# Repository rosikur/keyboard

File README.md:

# keyboard

I dont know what to call it so lets call it "keeb" because thats the name  of  the guide

This was my first keyboard , apart from my macropad ,the keyboard took 3 times , more on that on my Journal

## Features
- Us keyboard
- Del key with fn + Backspace
- 75 %
- Made with lots of hate and Caffeine
- Rotary Encoder
## How to assemble
First you go to jlcpcb and uplood the gerber files, i recommend black pcb colors
Then you go to Aliexpress and order all the parts from the BOM

In the meantime while it ships you start printing the Case,if your Printer is too small , half it or you can order it off print legion

Once everything is ready , you grab some solder and an iron , i recommend leaded solder makes it easier,firstly take your pi pico and add the  male pins,then put it trough and solder everything and snap off its legs outside

Then take your diodes,and turn the board around ,make sure the diodes are pointing  down in orientation and solder them,snap off its legs 

Then take your switchs,turn the board around and pit them all in and solder them one by one 

Last but not least ,add the rotary encoder and solder it

Also add the Stabalizers , watch a tiktok to put them togehter

put the ready board in the case add heated inserts and screw it together

add the key caps and youre done with assembly:D

## How to Software 
Set the Pi Pico to its Bootloader and connect it to your pc  take the uf2 zip and unzip , 

move the file to the pi labelled usb driver

thats it have fun! 

## Picture Gallary

## Bill of Materials

| Item | QNT | Price | Link | Details |
| --- | --- | --- | --- | --- |
| Switches | 162 | 13.39/45 * 4 = 53.56 EUR = 62.48 USD | [AliExpress](https://a.aliexpress.com/_EJTCEpM) | AKKO v3 pro cream blue |
| Keycaps | 2 sets | 16.99 EUR * 2 = 33.98 EUR = 39.64 USD | [AliExpress](https://a.aliexpress.com/_Eyr32DU) | Cuul MC keycaps |
| Diodes | 160 | 1.39 * 2 + duties = 5.78 | [AliExpress](https://a.aliexpress.com/_EGyImLY) | |
| Rotary Encoder | 2 | 6.49 + duties 3 EUR = 9.49 EUR | [AliExpress](https://a.aliexpress.com/_EjwhFqK) | |
| Orpheus Pico | 2 | 3.05 * 2 + duties = 9.10 | [AliExpress](https://a.aliexpress.com/_ExrMmQe) | In reality, it is a knockoff Pi Pico |
| PCB | | 37.39 | | |
| Cable | | 6.49 + duties = 9.49 | [AliExpress](https://a.aliexpress.com/_EwkdJdC) | |
| MX Stab | | 6.19 + duties = 9.19 | [AliExpress](https://a.aliexpress.com/_EHf4OAA) | |
| **Total** | | **167.98 EUR = 196.01 USD** | | |

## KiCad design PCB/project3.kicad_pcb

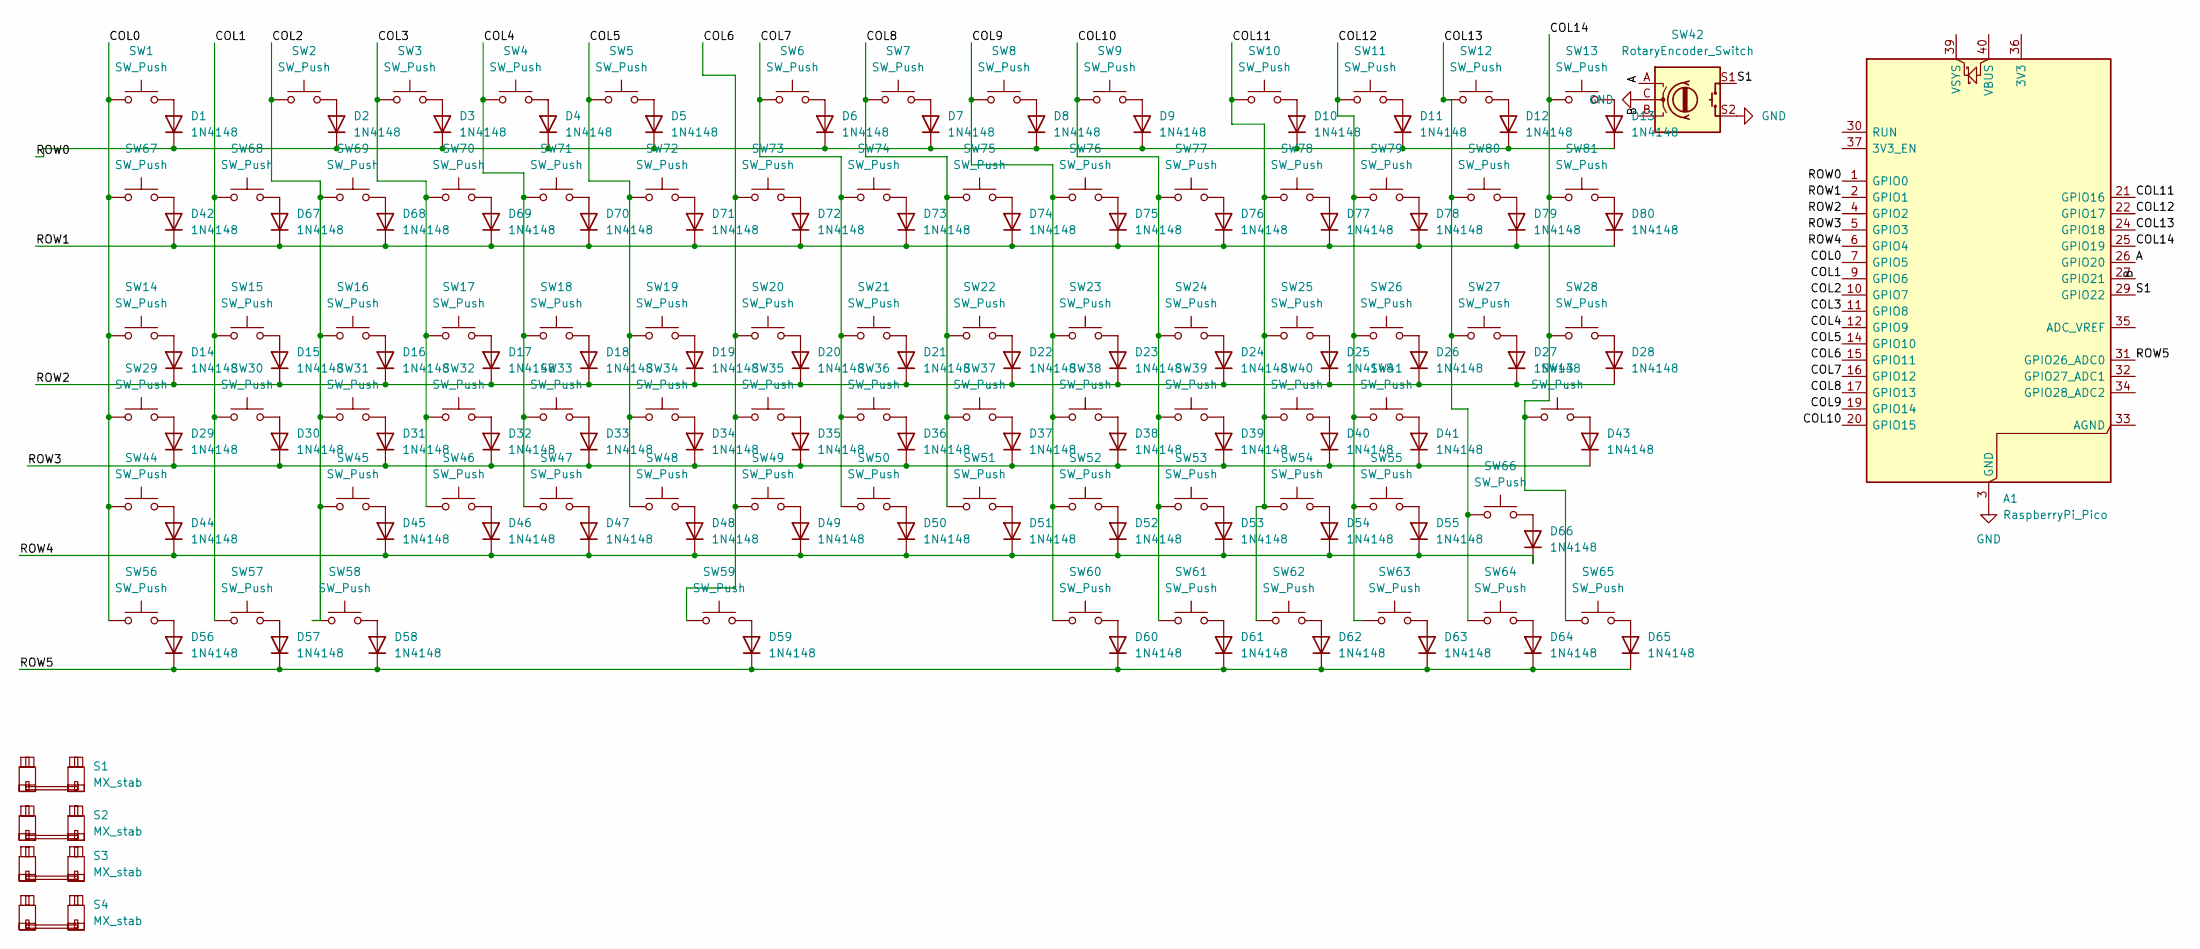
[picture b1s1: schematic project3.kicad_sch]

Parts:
A1: RaspberryPi_Pico; RaspberryPi_Pico_Common_Unspecified
D1, D2, D3, D4, D5, D6, D7, D8, D9, D10, D11, D12, D13, D14, D15, D16, D17, D18, D19, D20, D21, D22, D23, D24, D25, D26, D27, D28, D29, D30, D31, D32, D33, D34, D35, D36, D37, D38, D39, D40, D41, D42, D43, D44, D45, D46, D47, D48, D49, D50, D51, D52, D53, D54, D55, D56, D57, D58, D59, D60, D61, D62, D63, D64, D65, D66, D67, D68, D69, D70, D71, D72, D73, D74, D75, D76, D77, D78, D79, D80: 1N4148; D_DO-35_SOD27_P7.62mm_Horizontal
S1: MX_stab; STAB_MX_P_6.25u
S2, S3, S4: MX_stab; STAB_MX_2.25u
SW1, SW2, SW3, SW4, SW5, SW6, SW7, SW8, SW9, SW10, SW11, SW12, SW13, SW14, SW15, SW16, SW17, SW18, SW19, SW20, SW21, SW22, SW23, SW24, SW25, SW26, SW27, SW28, SW29, SW30, SW31, SW32, SW33, SW34, SW35, SW36, SW37, SW38, SW39, SW40, SW41, SW43, SW44, SW45, SW46, SW47, SW48, SW49, SW50, SW51, SW52, SW53, SW54, SW55, SW56, SW57, SW58, SW59, SW60, SW61, SW62, SW63, SW64, SW65, SW66, SW67, SW68, SW69, SW70, SW71, SW72, SW73, SW74, SW75, SW76, SW77, SW78, SW79, SW80, SW81: SW_Push; SW_MX_1u
SW42: RotaryEncoder_Switch; RotaryEncoder_Alps_EC11E-Switch_Vertical_H20mm

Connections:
/A: A1.26 (GPIO20), SW42.A
/B: A1.27 (GPIO21), SW42.B
/COL0: A1.7 (GPIO5), SW1.1, SW14.1, SW29.1, SW44.1, SW56.1, SW67.1
/COL1: A1.9 (GPIO6), SW15.1, SW30.1, SW57.1, SW68.1
/COL2: A1.10 (GPIO7), SW2.1, SW16.1, SW31.1, SW45.1, SW58.1, SW69.1
/COL4: A1.12 (GPIO9), SW4.1, SW18.1, SW33.1, SW47.1, SW71.1
/COL5: A1.14 (GPIO10), SW5.1, SW19.1, SW34.1, SW48.1, SW72.1
/COL6: A1.15 (GPIO11), SW20.1, SW35.1, SW49.1, SW59.1, SW73.1
/COL7: A1.16 (GPIO12), SW6.1, SW21.1, SW36.1, SW50.1, SW74.1
/COL8: A1.17 (GPIO13), SW7.1, SW22.1, SW37.1, SW51.1, SW75.1
/COL9: A1.19 (GPIO14), SW8.1, SW23.1, SW38.1, SW52.1, SW60.1, SW76.1
/COL10: A1.20 (GPIO15), SW9.1, SW24.1, SW39.1, SW53.1, SW61.1, SW77.1
/COL11: A1.21 (GPIO16), SW10.1, SW25.1, SW40.1, SW54.1, SW62.1, SW78.1
/COL12: A1.22 (GPIO17), SW11.1, SW26.1, SW41.1, SW55.1, SW63.1, SW79.1
/COL13: A1.24 (GPIO18), SW12.1, SW27.1, SW64.1, SW66.1, SW80.1
/COL14: A1.25 (GPIO19), SW13.1, SW28.1, SW43.1, SW65.1, SW81.1
/ROW0: A1.1 (GPIO0), D1.1 (K), D2.1 (K), D3.1 (K), D4.1 (K), D5.1 (K), D6.1 (K), D7.1 (K), D8.1 (K), D9.1 (K), D10.1 (K), D11.1 (K), D12.1 (K), D13.1 (K)
/ROW1: A1.2 (GPIO1), D42.1 (K), D67.1 (K), D68.1 (K), D69.1 (K), D70.1 (K), D71.1 (K), D72.1 (K), D73.1 (K), D74.1 (K), D75.1 (K), D76.1 (K), D77.1 (K), D78.1 (K), D79.1 (K), D80.1 (K)
/ROW2: A1.4 (GPIO2), D14.1 (K), D15.1 (K), D16.1 (K), D17.1 (K), D18.1 (K), D19.1 (K), D20.1 (K), D21.1 (K), D22.1 (K), D23.1 (K), D24.1 (K), D25.1 (K), D26.1 (K), D27.1 (K), D28.1 (K)
/ROW3: A1.5 (GPIO3), D29.1 (K), D30.1 (K), D31.1 (K), D32.1 (K), D33.1 (K), D34.1 (K), D35.1 (K), D36.1 (K), D37.1 (K), D38.1 (K), D39.1 (K), D40.1 (K), D41.1 (K), D43.1 (K)
/ROW4: A1.6 (GPIO4), D44.1 (K), D45.1 (K), D46.1 (K), D47.1 (K), D48.1 (K), D49.1 (K), D50.1 (K), D51.1 (K), D52.1 (K), D53.1 (K), D54.1 (K), D55.1 (K), D66.1 (K)
/ROW5: A1.31 (GPIO26_ADC0), D56.1 (K), D57.1 (K), D58.1 (K), D59.1 (K), D60.1 (K), D61.1 (K), D62.1 (K), D63.1 (K), D64.1 (K), D65.1 (K)
/S1: A1.29 (GPIO22), SW42.S1
GND: A1.3 (GND), A1.8 (GND), A1.13 (GND), A1.18 (GND), A1.23 (GND), A1.28 (GND), A1.38 (GND), SW42.C, SW42.S2
unnamed: D1.2 (A), SW1.2
unnamed: D2.2 (A), SW2.2
unnamed: D3.2 (A), SW3.2
unnamed: D4.2 (A), SW4.2
unnamed: D5.2 (A), SW5.2
unnamed: D6.2 (A), SW6.2
unnamed: D7.2 (A), SW7.2
unnamed: D8.2 (A), SW8.2
unnamed: D9.2 (A), SW9.2
unnamed: D10.2 (A), SW10.2
unnamed: D11.2 (A), SW11.2
unnamed: D12.2 (A), SW12.2
unnamed: D13.2 (A), SW13.2
unnamed: D14.2 (A), SW14.2
unnamed: D15.2 (A), SW15.2
unnamed: D16.2 (A), SW16.2
unnamed: D17.2 (A), SW17.2
unnamed: D18.2 (A), SW18.2
unnamed: D19.2 (A), SW19.2
unnamed: D20.2 (A), SW20.2
unnamed: D21.2 (A), SW21.2
unnamed: D22.2 (A), SW22.2
unnamed: D23.2 (A), SW23.2
unnamed: D24.2 (A), SW24.2
unnamed: D25.2 (A), SW25.2
unnamed: D26.2 (A), SW26.2
unnamed: D27.2 (A), SW27.2
unnamed: D28.2 (A), SW28.2
unnamed: D29.2 (A), SW29.2
unnamed: D30.2 (A), SW30.2
unnamed: D31.2 (A), SW31.2
unnamed: D32.2 (A), SW32.2
unnamed: D33.2 (A), SW33.2
unnamed: D34.2 (A), SW34.2
unnamed: D35.2 (A), SW35.2
unnamed: D36.2 (A), SW36.2
unnamed: D37.2 (A), SW37.2
unnamed: D38.2 (A), SW38.2
unnamed: D39.2 (A), SW39.2
unnamed: D40.2 (A), SW40.2
unnamed: D41.2 (A), SW41.2
unnamed: D42.2 (A), SW67.2
unnamed: D43.2 (A), SW43.2
unnamed: D44.2 (A), SW44.2
unnamed: D45.2 (A), SW45.2
unnamed: D46.2 (A), SW46.2
unnamed: D47.2 (A), SW47.2
unnamed: D48.2 (A), SW48.2
unnamed: D49.2 (A), SW49.2
unnamed: D50.2 (A), SW50.2
unnamed: D51.2 (A), SW51.2
unnamed: D52.2 (A), SW52.2
unnamed: D53.2 (A), SW53.2
unnamed: D54.2 (A), SW54.2
unnamed: D55.2 (A), SW55.2
unnamed: D56.2 (A), SW56.2
unnamed: D57.2 (A), SW57.2
unnamed: D58.2 (A), SW58.2
unnamed: D59.2 (A), SW59.2
unnamed: D60.2 (A), SW60.2
unnamed: D61.2 (A), SW61.2
unnamed: D62.2 (A), SW62.2
unnamed: D63.2 (A), SW63.2
unnamed: D64.2 (A), SW64.2
unnamed: D65.2 (A), SW65.2
unnamed: D66.2 (A), SW66.2
unnamed: D67.2 (A), SW68.2
unnamed: D68.2 (A), SW69.2
unnamed: D70.2 (A), SW71.2
unnamed: D71.2 (A), SW72.2
unnamed: D72.2 (A), SW73.2
unnamed: D73.2 (A), SW74.2
unnamed: D74.2 (A), SW75.2
unnamed: D75.2 (A), SW76.2
unnamed: D76.2 (A), SW77.2
unnamed: D77.2 (A), SW78.2
unnamed: D78.2 (A), SW79.2
unnamed: D79.2 (A), SW80.2
unnamed: D80.2 (A), SW81.2

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
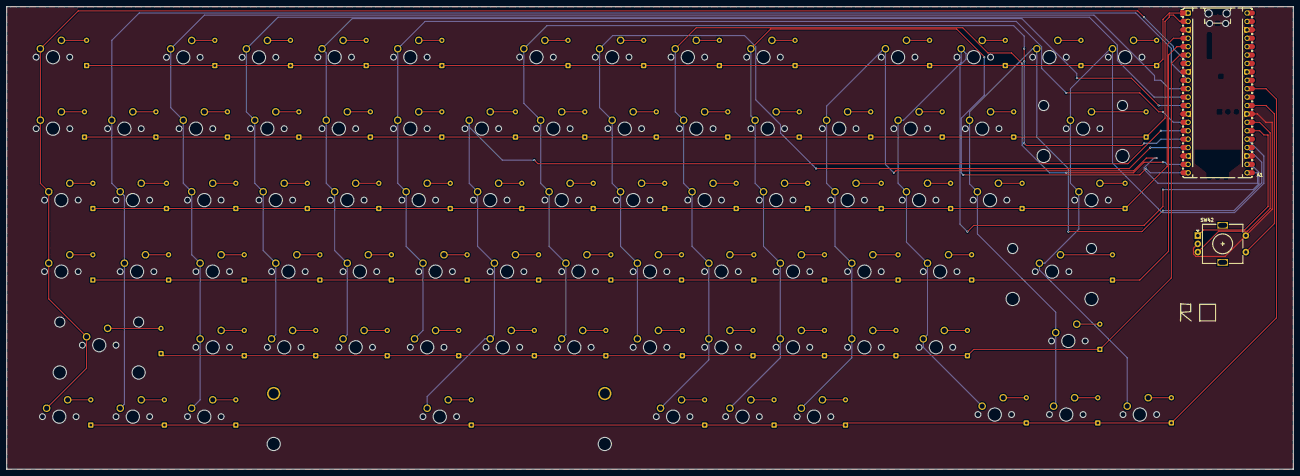
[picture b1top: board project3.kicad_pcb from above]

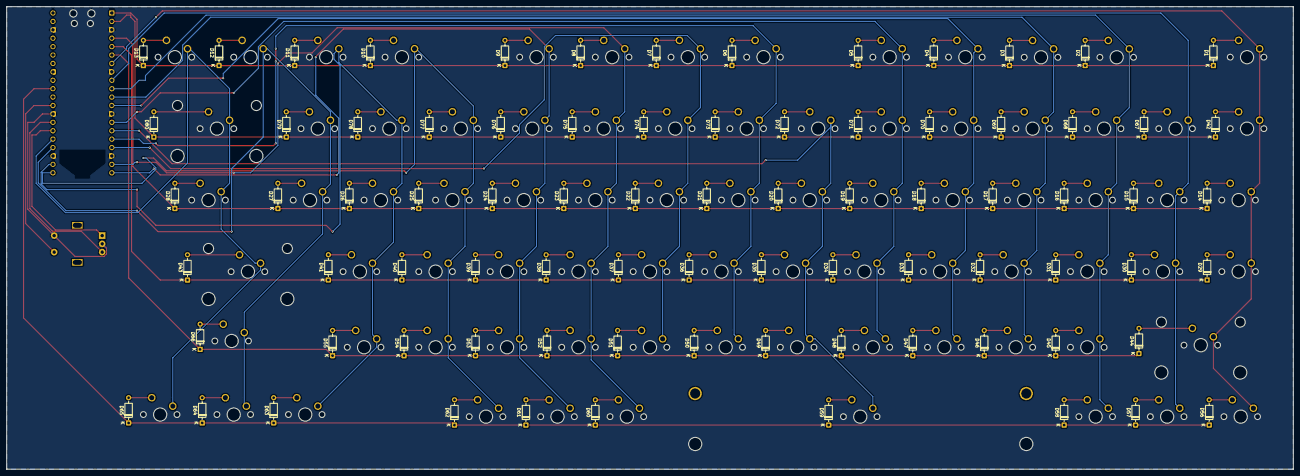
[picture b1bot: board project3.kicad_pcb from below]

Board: 2 copper layers, 388.6 x 139.7 mm, 166 parts (80 on the bottom side), 105 nets.
